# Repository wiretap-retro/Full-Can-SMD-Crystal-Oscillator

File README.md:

# Full Can SMD Crystal Oscillator
A full can crystal oscillator replacement using 3.3V SMD components for 5V systems.

\

## Info
This board is a full can crystal oscillator replacement for 5V systems. It uses 3.3v SMD components. It also features an enable/disable pin if your parent board requires it.

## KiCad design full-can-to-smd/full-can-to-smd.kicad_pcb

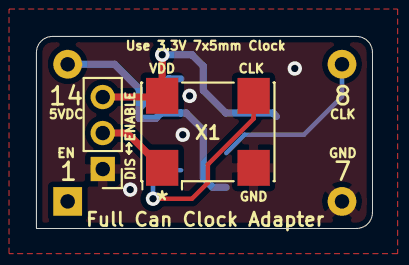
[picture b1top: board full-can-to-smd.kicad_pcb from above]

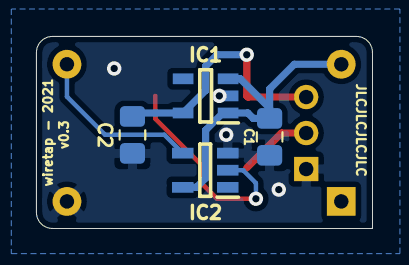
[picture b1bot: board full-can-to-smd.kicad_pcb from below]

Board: 2 copper layers, 18.7 x 10.7 mm, 7 parts (4 on the bottom side), 6 nets.

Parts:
C1, C2: 1uF; C_0805_2012Metric_Pad1.15x1.40mm_HandSolder
IC1: ADP1710AUJZ-3.3-R7; SOT95P280X100-5N
IC2: SN74LV1T34DBVRG4; SOT95P280X145-5N
J1: DISABLE; PinHeader_1x03_P2.00mm_Vertical
X0: CXO_DIP14; Oscillator_DIP-14
X1: ASCO; Oscillator_SMD_Abracon_ASV-4Pin_7.0x5.1mm

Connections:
/3.3VDC: C2.1, IC1.5, J1.3, X1.4
/3VCLK: IC2.2, X1.3
/5VCLK: IC2.4, X0.8
/5VDC: C1.1, IC1.1, IC1.3, IC2.5, X0.14
GND: C1.2, C2.2, IC1.2, IC2.3, J1.1, X0.7, X1.2
unnamed: J1.2, X1.1
